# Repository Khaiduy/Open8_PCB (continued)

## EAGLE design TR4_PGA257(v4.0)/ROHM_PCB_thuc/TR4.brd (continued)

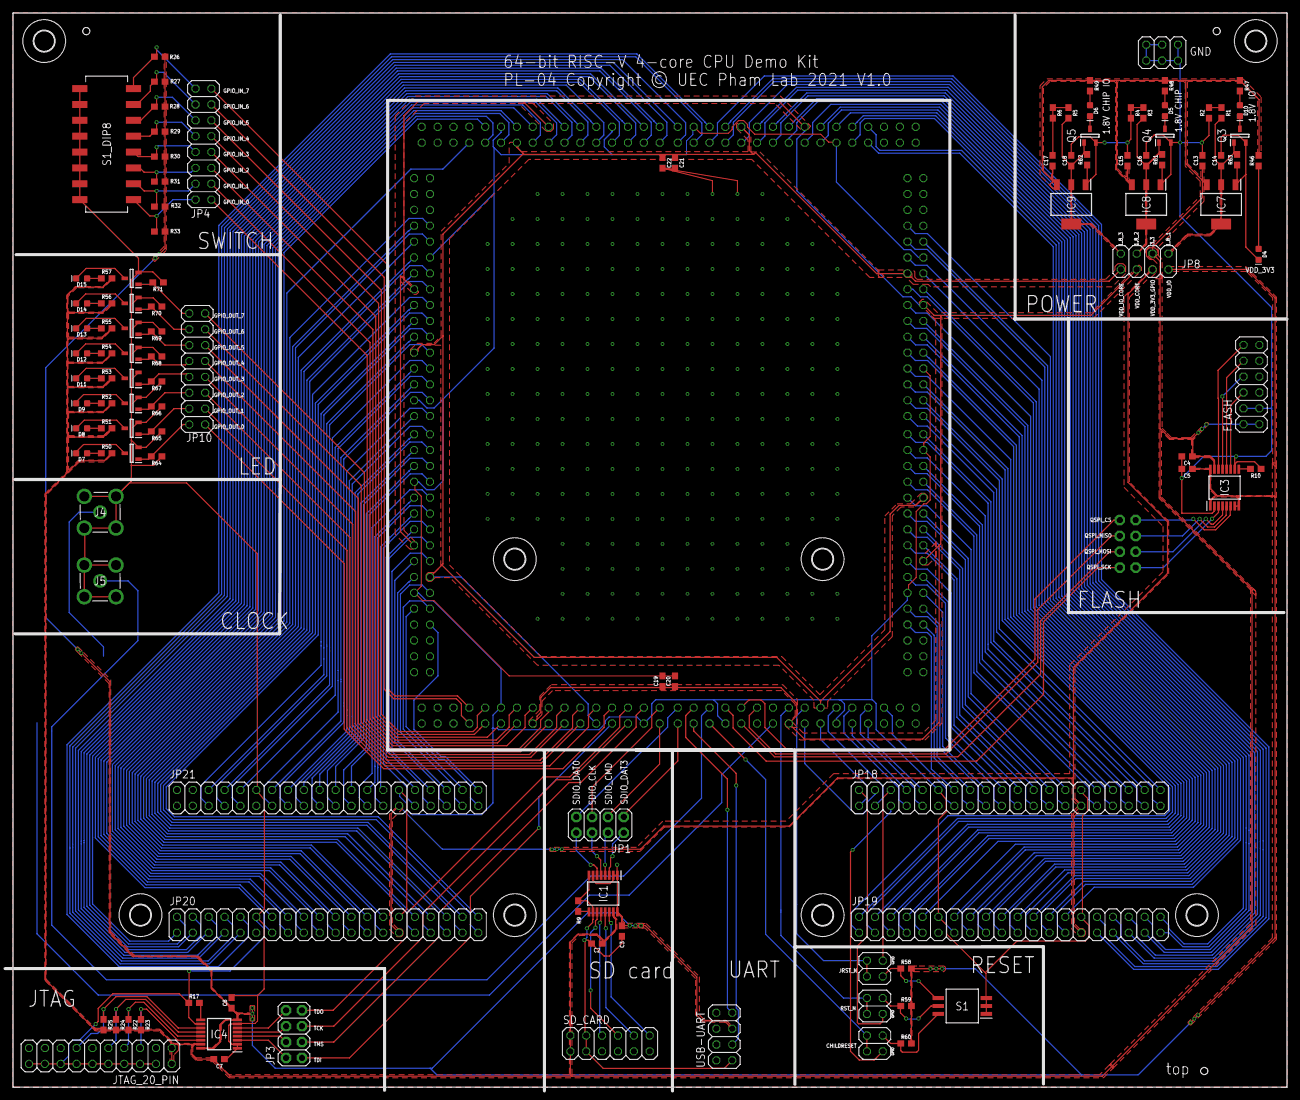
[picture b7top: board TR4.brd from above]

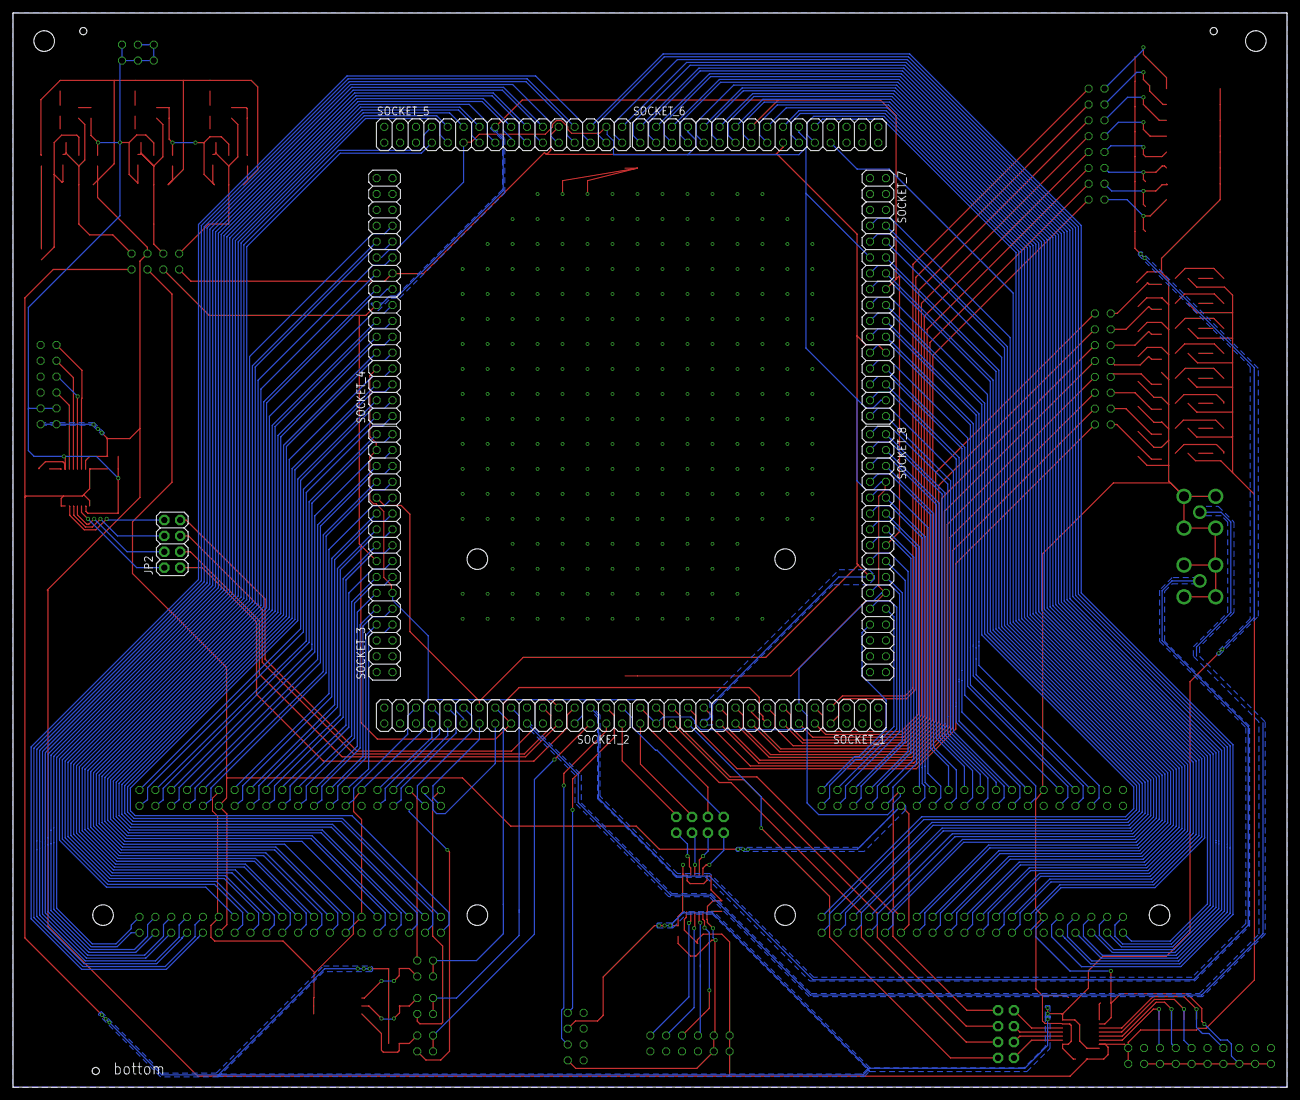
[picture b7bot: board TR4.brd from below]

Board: 2 copper layers, 204.0 x 172.0 mm, 130 parts (9 on the bottom side), 253 nets.

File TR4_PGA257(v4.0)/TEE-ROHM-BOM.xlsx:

Comment | Designator | Footprint | LCSC Part #（optional）
0.1uF | C1, C2, C3, C4, C5, C6, C19, C21 | 603 | C77055
100uF | C14, C16, C18 | 603
10KOHM | R7, R8, R9, R22, R23, R24, R25, R26, R27, R28, R29, R30, R31, R32, R33, R58, R5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 | 603 | C25804
10uF | C13, C15, C17, C20, C22 | 603 | C1691
15KOHM | R1, R3, R5 | 603 | C22809
Switch | S1_DIP8 | 2198LPST | C314503
330OHM | R46, R47, R48, R49, R50, R51, R52, R53, R54, R55, R56, R57 | 603 | C23138
6.8KOHM | R2, R4, R6 | 603 | C23212
BSH103,235 | Q3, Q4, Q5, Q6, Q7, Q8, Q9, Q10, Q11, Q12, Q13 | SOT-23-3 | C88711
DSHP03TSGET | S1 | SW-SMD | C50844
LED0 | D4, D5, D6, D7, D8, D9, D10, D11, D12, D13, D14, D15 | LED-0603 | C2286
LM1117IMPX-ADJ/NOPB | IC7, IC8, IC9 | SOT-223 | C19228
SN74AVC4T774RSVR | IC1, IC2, IC3 | UQFN-16 | C779392
